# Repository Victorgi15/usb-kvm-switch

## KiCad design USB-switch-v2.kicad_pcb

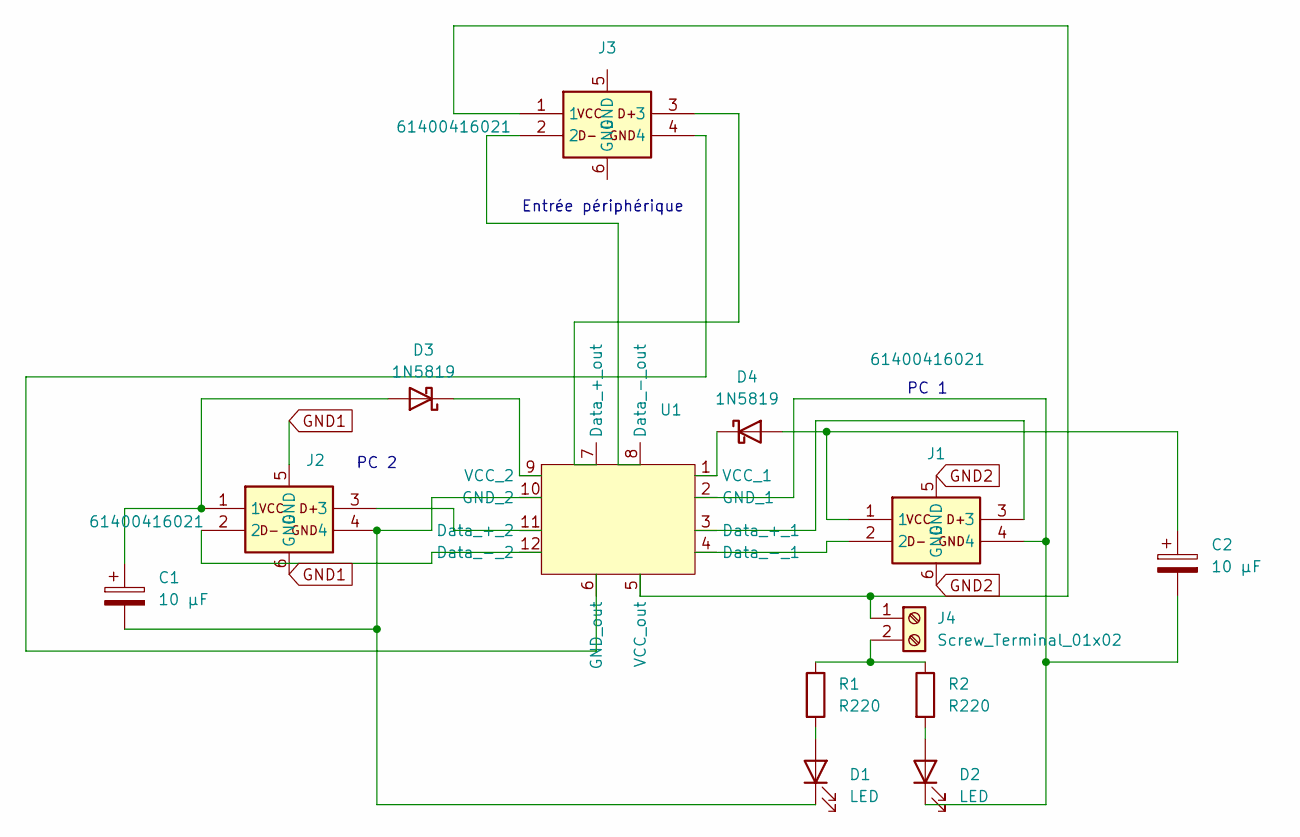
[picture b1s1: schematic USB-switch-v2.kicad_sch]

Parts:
C1, C2: 10 µF; C_Rect_L4.0mm_W2.5mm_P2.50mm
D1, D2: LED; LED_D5.0mm
D3, D4: 1N5819; D_DO-41_SOD81_P10.16mm_Horizontal
J1, J2, J3: 61400416021; USB-2.0-TYPE-A; Mouser Part Number 710-61400416021
J4: Screw_Terminal_01x02; TE_826576-2_1x02_P3.96mm_Vertical
R1, R2: R220; R_Axial_DIN0207_L6.3mm_D2.5mm_P7.62mm_Horizontal
U1: interupteur_12pins_v2

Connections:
GND1: J2.5 (GND), J2.6 (GND)
GND2: J1.5 (GND), J1.6 (GND)
unnamed: D1.2 (A), R1.2
unnamed: C1.2, D1.1 (K), J2.4, U1.10 (GND_2)
unnamed: D2.2 (A), R2.2
unnamed: C2.2, D2.1 (K), J1.4, U1.2 (GND_1)
unnamed: C1.1, D3.2 (A), J2.1
unnamed: D3.1 (K), U1.9 (VCC_2)
unnamed: C2.1, D4.2 (A), J1.1
unnamed: D4.1 (K), U1.1 (VCC_1)
unnamed: J3.1, J4.1, U1.5 (VCC_out)
unnamed: J4.2, R1.1, R2.1
unnamed: J1.3, U1.3 (Data_+_1)
unnamed: J2.3, U1.11 (Data_+_2)
unnamed: J3.3, U1.7 (Data_+_out)
unnamed: J1.2, U1.4 (Data_-_1)
unnamed: J2.2, U1.12 (Data_-_2)
unnamed: J3.2, U1.8 (Data_-_out)
unnamed: J3.4, U1.6 (GND_out)

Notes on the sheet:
PC 2
Entrée périphérique
PC 1

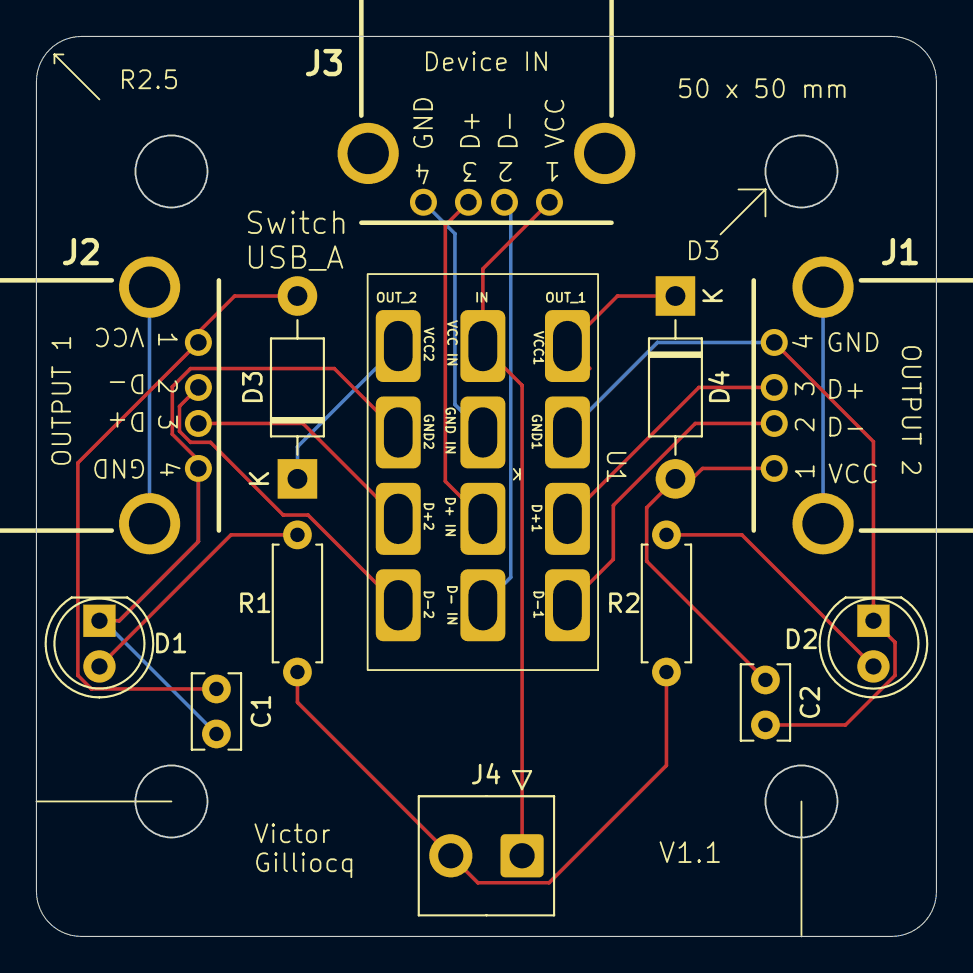
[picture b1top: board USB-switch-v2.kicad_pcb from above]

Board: 2 copper layers, 50.0 x 50.0 mm, 13 parts (0 on the bottom side), 19 nets.

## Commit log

2026-01-11 Add KiCad project files
2026-01-11 Add fabrication outputs
2026-01-11 Add backups and cache
2026-01-11 Add enclosure CAD and 3D exports
2026-01-11 Add original KiCad sources
2026-01-11 Add .gitignore for KiCad temp files
